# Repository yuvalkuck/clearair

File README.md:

# ClearAir — Intelligent AC Vent Fan Controller

An industrial-grade, real-time environmental control and safety monitoring system running on the **STM32G4** platform. The project is designed to capture ambient air particulates and track highly toxic electrode gases generated during industrial processes (such as welding, EDM, or plasma cutting) to dynamically regulate an AC ventilation fan using a solid-state TRIAC module.

---

## 📑 Table of Contents

- [System Architecture Overview](#-system-architecture-overview)
- [Power & Logic Integration](#-power--logic-integration)
  - [Power Budget (estimate)](#power-budget-estimate)
- [Target Gases & Environmental Indices](#-target-gases--environmental-indices)
  - [Planned Control Indices](#planned-control-indices)
- [Hardware Peripheral Mapping](#️-hardware-peripheral-mapping)
- [Software Architecture](#-software-architecture)
  - [Planned Safety Latch State Machine](#planned-safety-latch-state-machine)
  - [Execution Strategy](#execution-strategy)
  - [Message-queue asynchronous flow](#message-queue-asynchronous-flow)
  - [Sensor-Level Fan Control](#sensor-level-fan-control)
  - [Evacuate alarm](#evacuate-alarm)
- [Compensation & Normalization Models](#-compensation--normalization-models)
- [Safety Core & Fail-Safes](#-safety-core--fail-safes)
- [Roadmap](#️-roadmap)
- [STM32G474CEU6 Pin Plan (WeAct G4 Long)](#-stm32g474ceu6-pin-plan-weact-g4-long)
  - [Service → Pin Assignments](#service--pin-assignments)
  - [Reserved Pins (board / debugger — do not assign)](#reserved-pins-board--debugger--do-not-assign)
  - [Conflict Check](#conflict-check)

---

## 🚀 System Architecture Overview

To protect sensitive metal-oxide gas sensors from destructive metallic dust and electrode debris while keeping ambient tracking responsive, ClearAir uses a **dual-zone sampling topology**:

```mermaid
graph TD
    Ambient[Ambient Air] -->|Direct Ambient Draw| SPS30[Open Air Zone: SPS30 Sensor Element]
    Ambient -->|3-Meter Physical Pipeline| Filter[3M 2091 P100 Particulate Filter]
    Filter -->|Flow Restriction| FanF[Front Fan: 80 mm, 4-pin PWM]
    FanF -->|Pneumatic Delay Delivery| Chamber[Shielded Gas Chamber]
    
    subgraph Isolated Chamber
        Chamber --> MQ131[MQ131 Ozone Sensor]
        Chamber --> MiCS[MiCS-4514 CO / NO2 Sensor]
        Chamber --> BME680[BME680 Environmental Sensor]
    end

    Chamber -->|Exhaust| FanR[Rear Fan: 80 mm, 4-pin PWM, low-rpm standby]

    style Isolated Chamber fill:#f9f9f9,stroke:#333,stroke-width:2px
```

*   **Ambient Air Zone:** The `SPS30` particulate matter sensor rests directly in unshielded ambient air to capture raw particulate mass values before any extraction or filtration happens.
*   **Shielded Gas Chamber:** The `MQ131`, `MiCS-4514`, and `BME680` sensors are isolated inside an analytical testing container. A front fan pulls air through a 3-meter tube and draws it across a **3M 2091 P100 filter**. This removes 99.97% of airborne dust and metallic shards, delivering clean target gases to the metal-oxide sensor elements.
*   **Fans:** Two identical 80 mm (8025), 12 V, 4-pin PWM fans (Cooler Master `FA08025M12LPA` class, about 5800 rpm at full speed, about 0.66 A each). Both run all the time: the front fan sets the sampling flow, at a speed well below its 5800 rpm maximum. The rear fan, at the exhaust end of the chamber, runs at a low speed and keeps the chamber near ambient pressure. If the front fan's tach signal shows a failure, the rear fan speeds up so air still passes through the filter and the sensors are not exposed to unfiltered air. This failover is planned and not implemented in firmware yet. Each fan has its own PWM output and tach input (see the pin plan below).

---

## ⚡ Power & Logic Integration

*   **Mains Split & Supply Rails:** The 220VAC mains feed splits two ways: one branch goes to the RobotDyn TRIAC dimmer (fan phase control), the other to two AC-DC power supply modules, each 2 A and 36.4 x 70 x 23 mm: one outputs **12V** (safety buzzer and both 80 mm fans) and one outputs **5V** (WeAct G474CE Long board via its `P3` 5V pad, plus all sensors, the RobotDyn logic side, and the front-panel WS2812B LEDs). The **3.3V** rail comes from the WeAct board's on-board regulator. Both 80 mm fans run from the 12V rail through the relay `K1` (Panasonic ALDP112, 12 V coil, 1 Form A, 3 A at 30 V DC): the relay contact feeds the fans' 12V pins (`M2` and `M3` pin 2, net `FAN_12V`), so they run whenever the relay is closed. `PB5` (`FILTER_FAN_POWER`) drives `Q6` (2N2222A) through `R41` (1 kΩ); `Q6` switches the coil to GND, `D3` (1N4148) is the flyback diode and `R44` (10 kΩ) keeps the relay open while the pin is not driven, so the fans have no power until the firmware sets `PB5` high. Each fan's PWM and tach wires go to the STM32 (see the pin plan); the fan GND is common with the STM32 GND.
*   **Electrical Noise Isolation:** The internal 5V heating elements of the gas sensors are powered directly from the external 5V supply rail rather than drawing from the MCU. This layout keeps heavy electrical switching current ripples completely away from the sensitive STM32 analog circuitry.
*   **Logic Interfacing:** The `I2C1` bus uses 4.7 kΩ pull-up resistors tied strictly to the STM32's 3.3V rail. The 5V-powered modules (MQ131, MiCS-4514, RobotDyn dimmer) send their outputs (MQ131 `AO`, MiCS-4514 `RED`/`NOX`, RobotDyn `Z-C`) through passive 1.8 kΩ (series) / 3.3 kΩ (to GND) voltage dividers, which drop a 5V signal to ~3.24V, under the 3.3V GPIO/ADC limit.
*   **Front Panel:** The STM32 drives the panel itself; there is no second controller. Six WS2812B RGB LEDs (5 V, one per metric: IAQ, O3, PM2.5, PM10, CO, NO2) form one chain on header `J9` (1 +5V, 2 DIN, 3 GND). Their data comes from `PA6` (`LED_DATA`, `TIM16_CH1` PWM fed by DMA at 800 kHz) through one gate of a 74AHCT125N (`U6`, in a DIP-14 socket, powered from 5 V), because the WS2812B needs at least 0.7 x 5 V = 3.5 V on DIN, more than a 3.3V pin gives. A 330 Ω resistor (`R25`) sits in series with DIN, `C27` (220 µF) buffers the LED supply at `J9`, and `C26` (100 nF) decouples `U6`. The three unused gates have their inputs on GND and `OE` on +5V. Each LED shows its metric's danger level by color and blinks while the buzzer alarm runs; the firmware caps the brightness. An I2C text display connects to header `J10` (1 3V3, 2 GND, 3 SDA, 4 SCL) on `I2C2`, shared with the RTC; the firmware does not use it yet, and once it does, the RTC driver needs a bus lock. Use a 3.3V display (OLED), or remove the 5V pull-ups of an LCD backpack. Four push buttons connect to header `J11` (1-4 `KEY1`-`KEY4`, 5 GND); each button shorts its pin to GND. The resistor ladder is on the board: `R26` (10 kΩ) pulls the `PB11` node (`BUTTONS_ADC`, `ADC2_IN14`) up to 3.3V, and each key pin connects to that node through its own resistor (`R27` 1 kΩ, `R28` 3.3 kΩ, `R29` 6.8 kΩ, `R30` 15 kΩ), so one ADC pin reads all four keys: none 3.30 V, KEY1 0.30 V, KEY2 0.82 V, KEY3 1.34 V, KEY4 1.98 V. `C28` (100 nF) filters the node. With two keys pressed, the lower-numbered key wins. The firmware does not read the keys yet. Four more push buttons, `SW3`-`SW6`, sit on the board as test buttons with a second ladder on `PA4` (`FORCE_STATES_SW`, `ADC2_IN17`): `R31` (10 kΩ) pulls the node up to 3.3V, `R32` 1 kΩ, `R33` 3.3 kΩ, `R34` 6.8 kΩ and `R35` 15 kΩ connect the keys, `C29` (100 nF) filters it, so the levels are the same as above. They test the system: `TEST1` fan off, `TEST2` lower fan speed, `TEST3` higher fan speed, `TEST4` 100% fan plus the buzzer. A standby push button `SW7` (on board) and the 2-pin header `J12` (1 `STANDBY_SW`, 2 GND, for an external switch) are wired in parallel to `PB1` (`STANDBY_SW`); either one pulls the pin to GND, and the MCU pull-up holds it high. Standby is meant to turn off all fans (`PB5` low opens the relay `K1`, and the AC fan stays off) and the buzzer; the firmware does not do this yet. A press only counts when the button is released: the standby event fires on the release, after debounce, and each event toggles standby and the LEDs. Two through-hole status LEDs sit on the board, both on `PB0` (`STANDBY_LED`) with no transistor: the red `D2` goes from the `PB0` node through `R38` (330 Ω) to GND, the green `D1` goes from 3V3 through `R37` (330 Ω) to the `PB0` node, and `R40` (2.2 kΩ) pulls the node up to 3V3. The red LED is therefore on by default, also while the MCU resets and its pin floats; `PB0` high keeps red on and green off, `PB0` low turns red off and lights green. The safety buzzer stays on its own GPIO (see Safety Core & Fail-Safes), so it still sounds if the LEDs or the display fail.
*   **Real-Time Clock (RTC):** A PCF8563 on a HW-689 module (I2C address 0x51, 1.0 to 5.5 V) has its own bus, `I2C2` (`PC4` SCL, `PA8` SDA), with 4.7 kΩ pull-ups to 3.3V; its `COT` and `INT` pins stay unconnected. Only the RTC task uses that bus, so it needs no lock shared with the sensor tasks. The module sits off the perfboard and connects through the 4-pin header `J7` (VCC 3V3, GND, SDA, SCL). A CR1220 cell on the module keeps the clock running during a power loss. Before fitting a non-rechargeable cell, power the module with no cell and check that the cell's + contact reads about 0 V: some RTC modules charge the cell, which would damage a CR1220. The driver is `device/rtc` (`ClockRtc`). Only elapsed time matters, so the clock is never set to the real time: if the `VL` bit says the clock was lost, it restarts at 2000-01-01 00:00. The `rtcTask` writes a "last alive" stamp (minute, hour, day, weekday) once a minute into the four alarm registers, with every alarm-enable bit off so the alarm never fires. At boot, `configure()` compares the clock with the stamp: under 1 hour offline means the 30 minute MQ131 warm-up, and 1 hour or more, a lost clock, an unreadable stamp or an RTC that does not answer means the 48 hour preheat. The stamp has no month, so a gap is only counted when the stamp is from the same day or the day before. The `PB14` button still forces the cold boot. A power cut during the 48 hour preheat followed by a restart under 1 hour later only gets the 30 minute warm-up.
*   **Gas Sensor Heaters:** The MQ131 heater needs a constant 5 V (datasheet: VH 5.0 V ±0.1 V, 34 Ω, up to 900 mW) and over 48 h of preheat after a cold start, so the module VCC and GND are wired straight to the 5 V rail and GND: it is always on and nothing switches it. The MiCS-4514 heaters run on constant power from VCC through the module's own resistors (82 Ω RED, 51 + 82 Ω OX). Its `PRE` pin is tied to GND, so the boost (which shorts the 51 Ω and runs the OX heater near 75 mW, above the 50 mW maximum) is never used. Tie `PRE` to GND only after checking it has the 100 kΩ pull-down to GND (unpowered, `PRE` to GND about 100 kΩ).

### Power Budget (estimate)

Typical datasheet values, not measurements (±20%). STM32 at 170 MHz (`clearair.ioc`).

**5V rail**

| Load | Typical | Peak / max |
| :--- | :--- | :--- |
| WeAct G474CE Long (STM32G474 @ 170 MHz + on-board regulator + user LED; the 3.3V LDO passes the 3V3 load through, so it is counted in the next row) | ~40 mA | 60 mA |
| 3V3 loads via the on-board regulator (BME680 incl. gas-heater pulses, I2C pull-ups, fan tach pull-ups, PCF8563 RTC, two button ladders 0.3 mA max each, green or red status LED about 3-4 mA, `R40` pull-up 1.5 mA while `PB0` is low, `R41` base current 2.6 mA while the fans run) | ~11 mA | 22 mA |
| SPS30 (measuring) | 60 mA | 80 mA |
| MQ131 heater + module (always on, 5 V) | ~170 mA | 185 mA |
| MiCS-4514 (RED + OX heaters + module, `PRE` tied to GND, no boost) | ~60 mA | 65 mA |
| RobotDyn logic side (Z-C opto + PSM) | ~5 mA | 15 mA |
| 1.8k/3.3k dividers (×4) | ~5 mA | 5 mA |
| 74AHCT125N level shifter (`U6`) | <1 mA | 1 mA |
| WS2812B LEDs on `J9` (×6; about 1 mA idle each, one color at reduced brightness typical, all white at full brightness max) | ~70 mA | 360 mA |
| I2C display on `J10` (3.3V OLED, not fitted yet; through the 3.3V regulator) | ~20 mA | 30 mA |
| **Total** | **~440 mA ≈ 2.2 W** | **~830 mA ≈ 4.1 W** |

The 5V total has no fan, because both fans run from the 12V rail. The STLINK-V3MINIE debugger is powered over its own USB and only senses the board's 3.3V on `T_VCC`, so it adds no load to either rail. The G474 board row is an estimate, not a datasheet value: measure the board current on the bench.

**12V rail**

| Load | Typical | Peak / max |
| :--- | :--- | :--- |
| 12V buzzer (active type, only while the alarm sounds) | 30 mA | ~100 mA (loud siren type) |
| Front 80 mm fan (4-pin PWM) | not measured, below the label current at reduced speed | ~660 mA (label) |
| Rear 80 mm fan (4-pin PWM) | not measured, below the label current at low speed | ~660 mA (label) |
| Relay `K1` coil (ALDP112, 720 Ω, while the fans run) | 17 mA | 17 mA |
| **Total** | **not measured** | **~1.44 A ≈ 17 W** |

**PSU sizing:** 5V ≥ 1 A, 12V ≥ 1.5 A. The two 2 A modules cover both rails: the 5V module has about 3 times margin over the 0.61 A peak, and the 12V module has about 30% margin over the 1.44 A peak, so measure the real fan current and the startup surge on the bench. The extra 5V headroom covers cold-heater inrush on the MQ131 and MiCS-4514. The gas-sensor heaters are ~50% of the 5V load (230 of 450 mA typical). The fan rows use the label current quoted in the listing; replace them with measured values.

---

## 📊 Target Gases & Environmental Indices

| Sensor | Target Media | Application / Electrode Coverage |
| :--- | :--- | :--- |
| **SPS30** | PM1.0, PM2.5, PM4.0, PM10 | Monitors metallic fumes, hexavalent chromium particulates, manganese dust, and airborne ash before it reaches the filters. |
| **MQ131** | Ozone ($O_3$) | Tracks $O_3$ gas generated by intense ultraviolet (UV) radiation when open electric arcs ionize ambient oxygen molecules. |
| **MiCS-4514** | Carbon Monoxide ($CO$) & Nitrogen Dioxide ($NO_2$) | Measures toxic shielding gas breakdown products, incomplete combustion ($CO$), and high-temperature thermal fixation byproducts ($NO_2$). |
| **BME680** | VOCs, Sulfur Compounds, $H_2$ Gas | Utilizes the **Bosch BSEC2 library** to track complex vapor emissions coming from cutting fluids, dielectric oils, and insulating resins. |

### Planned Control Indices

Not implemented yet. Fan control today uses per-metric thresholds with no blended index (see [Sensor-Level Fan Control](#sensor-level-fan-control)).

*   **Chamber Air Quality Index (AQI):** A multi-variable matrix blending $CO$, $NO_2$, and BSEC2 $VOC$ data into a single risk metric to determine basic ventilation speeds.
*   **Oxidizing Gas Index (OGI):** A high-priority index tracking the sum of $O_3$ and $NO_2$ gas streams, mirroring extreme electrode ionization states.
*   **Filter Loading Index (FLI):** Calculated from the delta ratio between raw outdoor $SPS30$ values and internal $BME680$ barometric pressure drops, triggering a warning when the physical filter element is clogged.

---

## 🛠️ Hardware Peripheral Mapping

The full wiring schematic is in [`hardware/WeAct-G474CE-Long/clearair.kicad_sch`](hardware/WeAct-G474CE-Long/clearair.kicad_sch) (KiCad 10).

The pin assignments (STM32G474) are in [Service → Pin Assignments](#service--pin-assignments). The old NUCLEO-F446RE board is documented in [`doc/board_stm32f466.md`](doc/board_stm32f466.md).

---

## 🧠 Software Architecture

The software stack runs on top of a priority-preemptive FreeRTOS kernel. It segments slower sensor processing delays from the real-time, time-critical AC phase-angle modulation routines:

```mermaid
graph TD
    %% High-Voltage Side
    subgraph HV [HIGH-VOLTAGE AC SIDE - 50Hz]
        AC_Mains[220V Mains AC]
        AC_Fan[AC FAN MOTOR]
    end

    %% Low-Voltage Side
    subgraph LV [LOW-VOLTAGE CONTROL SIDE - 5V / 3.3V / 12V]
        %% Power Domain
        PSU[AC-DC PSU 12V / 5V]
        Power_5V[5V Power Rail]
        Power_12V[12V Power Rail]
        LDO_33[WeAct On-Board 3.3V Regulator]
        Buzzer_12[12V BUZZER]
        Fan_Front[Front Fan: 80 mm 4-pin PWM]
        Fan_Rear[Rear Fan: 80 mm 4-pin PWM]
        Trans_2N2222[NPN 2N2222A Transistor]
        GND[System GND]
        
        %% Microcontroller Internal Modules
        subgraph STM32 [STM32G4 MCU]
            EXTI[EXTI Line]
            Timer_B[Timer B Phase-Cut]
            PWM_T[TIM1 PWM 25 kHz: CH3 PA10, CH2 PA9]
            Tach_T[TIM2 input capture: CH1 PA5, CH2 PB3]
            subgraph RTOS [FreeRTOS Tasks]
                T1[Task 1: SPS30]
                T2[Task 2: BME680]
                T3[Task 3: MQ131]
                T4[Task 4: MiCS4514]
                T5[Task 5: Central Control]
            end
        end
        
        %% Isolation Barriers
        ZC_Circ[Zero-Crossing Circuit]
        TRIAC_Dim[Isolated TRIAC Dimmer]
    end

    %% Manual Controls
    Reset_Btn[External Reset Button]
    BootSel_Btn[External Boot-Select Button]

    %% Future Visualization Stage
    subgraph VIZ [FRONT PANEL]
        Level_Shift[74AHCT125N 3.3V to 5V buffer]
        LED_Array[6x WS2812B status LEDs]
        Display[I2C display on J10, future]
    end

    %% Power Routing Connections
    AC_Mains -->|Mains Feed| ZC_Circ
    AC_Mains -->|Mains Feed| TRIAC_Dim
    AC_Mains -->|Mains Feed| PSU
    PSU --> Power_5V
    PSU --> Power_12V
    Power_5V -->|P3 5V pad| LDO_33
    LDO_33 -->|3.3V Core VCC| STM32
    Power_12V -->|12V VCC| Buzzer_12
    Power_12V -->|12V + GND| Fan_Front
    Power_12V -->|12V + GND| Fan_Rear

    %% Fan Speed Control and Tach Feedback (firmware not implemented yet)
    PWM_T -->|PWM, PA10| Fan_Front
    PWM_T -->|PWM, PA9| Fan_Rear
    Fan_Front -->|Tach, PA5, 10k pull-up to 3.3V| Tach_T
    Fan_Rear -->|Tach, PB3, 10k pull-up to 3.3V| Tach_T

    %% Signal and Control Connections
    ZC_Circ -->|Opto-Isolated Pulse| EXTI
    EXTI -->|Trigger Reset| Timer_B
    Timer_B -->|Opto-Isolated Gate| TRIAC_Dim
    TRIAC_Dim -->|Phase-Cut Output| AC_Fan
    
    T5 -->|GPIO Output| Trans_2N2222
    Buzzer_12 -->|Low side| Trans_2N2222
    Trans_2N2222 -->|Emitter| GND

    T5 -->|PA6 TIM16 PWM + DMA| Level_Shift
    Level_Shift -->|5V DIN, 330 ohm| LED_Array
    T5 -->|I2C2 PC4/PA8, future| Display

    Reset_Btn -->|NRST| STM32
    BootSel_Btn -->|PB2, read once at boot| STM32
```
### Planned Safety Latch State Machine

This is the intended design, **not what the firmware does today**. The implemented behavior is in [Sensor-Level Fan Control](#sensor-level-fan-control): there is no 30 s countdown, no latch, and the buzzer turns off again when the air improves. The latch and the manual-reset requirement are still to do.

```mermaid
stateDiagram-v2
    [*] --> STATE_NORMAL
    
    state STATE_NORMAL {
        [*] --> WakeUp
        WakeUp --> Receive_Queue : New Reading Posted
        Receive_Queue --> Update_Latest
        Update_Latest --> Calculate_Fan_Curves
        Calculate_Fan_Curves --> Check_Max_Speed : Find Maximum Target Speed (0-100%)
    }
    
    Check_Max_Speed --> STATE_NORMAL : Target Speed < 100%\n[Set FanSpeed = Target Speed, Reset Counter = 30s]
    Check_Max_Speed --> STATE_VENTING_MAX : Target Speed == 100%\n[Set FanSpeed = 100%, Load Counter = 30s]
    
    state STATE_VENTING_MAX {
        [*] --> Evaluate_Trends
        Evaluate_Trends --> Reset_Counter : Metrics improving vs previous second
        Reset_Counter --> Check_Threshold : Values drop below 100%?
        Check_Threshold --> STATE_NORMAL : Yes
        Check_Threshold --> Evaluate_Trends : No
        
        Evaluate_Trends --> Decrement_Counter : Metrics flat or rising
        Decrement_Counter --> Check_Timeout
        Check_Timeout --> Evaluate_Trends : Counter > 0
    }
    
    Check_Timeout --> STATE_EVACUATE_LATCHED : Counter == 0
    
    state STATE_EVACUATE_LATCHED {
        [*] --> Lock_System
        Lock_System --> Force_Buzzer_High : Drive Buzzer GPIO Pin HIGH
        Force_Buzzer_High --> Stay_Locked : Fan locked at 100% / Ignore sensors
        Stay_Locked --> [*] : Requires Manual Hardware Reset
    }

```
### Execution Strategy
*   **Boot Mode Selection:** Before any sensor `configure()` call runs, `appStartDefaultTask` reads the `PB2` boot-select button once and then configures the RTC (`device/rtc`). It's a cold boot when the button is held, or when the RTC shows 1 hour or more offline (or cannot tell, see Real-Time Clock above); otherwise a warm boot. On a warm boot, MQ131 and MiCS-4514 run their normal (short) warm-up before publishing readings; on a cold boot, each runs its own extended warm-up/soak in parallel (see `device/o3sensor` and `device/co1no2`) — none of this is persisted across reboots.
*   **Aggregate Update Cadence:** Individual sensor tasks post to the queue at their own native rate (`SPS30` every 1.0s, `BME680` every 3.0s, `MQ131`/`MiCS-4514` every 20ms), but the system as a whole pushes an updated aggregate `CollectedAirData` snapshot roughly every ~5 seconds for downstream consumers (telemetry, the status LEDs, and the future display).
*   **Low-Overhead Data Capture:** `ADC1` runs continuously in multi-channel Scan Mode handled via DMA. It updates a local 3-element array in RAM with fresh voltages from the `MQ131` and `MiCS-4514` sensors without generating any CPU overhead.
*   **AC Phase Control Loop:** (implemented in `device/fanmotor`, it bypasses the RTOS)
    1. The AC power wave crosses zero volts and the RobotDyn zero-cross output pulls the `ZC_INPUT` pin low.
    2. The falling-edge external interrupt runs `HAL_GPIO_EXTI_Callback`, which calls `onZeroCross()`. If the fan speed is 0 it returns and the gate stays low.
    3. Otherwise it resets the `TIM3` counter, loads the current phase delay into `TIM3->ARR` and starts the `TIM3` update interrupt.
    4. When `TIM3` expires, its interrupt calls `onGateCompareMatch()`, which pulses the TRIAC gate pin (`TRIAC_DIMMER`) high for about 100 µs.
    5. `speedPercent()` (called from the control loop) sets the delay: 50% maps to a long delay (low power) and 100% to a short one, see [Sensor-Level Fan Control](#sensor-level-fan-control).

---

### Message-queue asynchronous flow
```mermaid
graph TD
    %% Asynchronous Inputs
    subgraph Loops [ASYNCHRONOUS INDEPENDENT SENSOR LOOPS]
        T1[Task 1: SPS30 Particulate I2C]
        T2[Task 2: BME680 Gas Plate I2C]
        T3[Task 3: MQ131 Ozone Analog ADC]
        T4[Task 4: MiCS4514 Dual Gas Analog]
    end

    %% Central Message Queue
    subgraph Buffer [FREERTOS MESSAGE QUEUE]
        direction TB
        Queue[[xSensorQueue]]
    end

    %% Sync / Control Layer
    subgraph Decision [PROCESSING & DECISION ENGINE]
        T5[Task 5: Central Controller — evaluates each reading on arrival]
        FanSpeed[Global Fan Speed Variable 0-100%]
        BuzzerPin[GPIO Pin Latch to 2N2222A Base]
        LED_Out[WS2812B status LEDs via TIM16 + DMA]
    end

    %% Hardware Real-Time Layer
    subgraph ISR_Layer [REAL-TIME HARDWARE TIMING LAYER - Bypasses RTOS]
        ZC_Pulse[Zero-Crossing Pulse Input]
        EXTI_ISR[EXTI Hardware Interrupt]
        Timer_ISR[STM32 Timer B Interrupt]
        TRIAC_Gate[Fires Pulse to Isolated TRIAC]
    end

    %% Async Data flow
    T1 -->|Posts reading every 1.0s| Queue
    T2 -->|Posts reading every 3.0s| Queue
    T3 -->|Posts reading every 20ms| Queue
    T4 -->|Posts reading every 20ms| Queue

    %% Central Decision flow
    Queue -->|Receives Each Reading| T5
    T5 -->|Updates| FanSpeed
    T5 -->|Drives HIGH at Evacuate level| BuzzerPin
    T5 -->|Level color per metric| LED_Out

    %% Precise Timing Hardware Loop
    ZC_Pulse --> EXTI_ISR
    EXTI_ISR -->|Resets and Restarts| Timer_ISR
    FanSpeed -.->|Read microsecond duration| Timer_ISR
    Timer_ISR -->|Delays Phase-Cut| TRIAC_Gate
```

### Sensor-Level Fan Control

The control loop (`mainSensorsMsgLoop` in `Core/Src/control_center.cpp`) turns every sensor reading into a danger level and a requested fan speed. The fan follows the worst metric.

**Per metric.** Each metric (BME680 IAQ, MQ131 ozone, SPS30 PM2.5, SPS30 PM10, MiCS-4514 CO, MiCS-4514 NO2) has four thresholds, in the metric's own unit:

| Threshold | Meaning |
| :--- | :--- |
| `fanOff` | A running fan keeps running until the reading drops below this value. It sits slightly below `fanOn`, so the fan does not switch on and off when a reading hovers around the turn-on point. |
| `fanOn` | A stopped fan turns on, at the minimum speed (50%), when the reading reaches this value. |
| `fanMax` | The fan reaches 100% at this value. Between `fanOn` and `fanMax` the speed rises linearly from 50% to 100%. |
| `evacuate` | At or above this value the evacuate alarm starts (see [Evacuate alarm](#evacuate-alarm)). It is at or above `fanMax`, so the fan is already at full speed when the alarm sounds. |

These give each metric one of three danger levels:

| Level | Condition | Fan | Buzzer |
| :--- | :--- | :--- | :--- |
| `Off` | Below `fanOn` (or below `fanOff` if the fan is already running) | Off | Off |
| `Ventilate` | From `fanOn` up to `evacuate` | 50% to 100%, proportional to the reading | Off |
| `Evacuate` | At or above `evacuate` | 100% | Alarm: 60 s on, then 30 s off / 10 s on repeating |

**Across metrics.** Every reading that arrives updates only its own metrics in a shared structure that holds the latest level and requested fan speed of each metric. When the loop finishes handling a message, it evaluates the whole structure: the fan speed is the highest requested by any metric, and the evacuate alarm starts if any metric is at `Evacuate`. The fan and buzzer are only written when the result changes.

**Kick-start.** A stopped motor cannot start at 50% speed. When the fan turns on from off, it first runs at 100% for a fixed spin-up time (`FAN_KICKSTART_MS`), then drops to the requested speed. The fan has no tachometer, so this is a timer, not a measured speed. If the air becomes clean during the spin-up, the fan stops straight away. The loop waits on the queue with a timeout while a spin-up runs, so the fan drops to its target on time even if no sensor message arrives.

**Fan speed to power.** The fan speed percentage maps linearly to the TRIAC firing delay in `device/fanmotor` (50% = `TRIAC_MIN_POWER_DELAY_US`, 100% = `TRIAC_MAX_POWER_DELAY_US`). It is not a power percentage. The 8" fan is an 80 W, 220 V capacitor-run AC motor, which stalls or hums at low voltage, so the minimum delay is set to give roughly 60% of mains RMS voltage at the 50% setting. That value is an estimate from the firing-angle curve and must be confirmed on the bench.

```mermaid
flowchart TD
    Msg[Sensor reading arrives on the queue] --> Update[Update only that sensor's metrics:<br/>level + requested fan %]
    Timeout[Spin-up or alarm timer expires<br/>queue wait timeout] --> Eval
    Update --> Eval[Evaluate all metrics]
    Eval --> Worst[Worst level and highest requested fan %]

    Worst --> Lvl{Worst level}
    Lvl --> Alarm[Evacuate alarm cycle<br/>see Evacuate alarm]

    Worst --> Fan{Requested fan %}
    Fan -->|0 and fan stopped| Stay[Fan stays off]
    Fan -->|0 and fan running| Stop[Stop fan, cancel any spin-up]
    Fan -->|more than 0, fan stopped| Kick[Kick-start: set 100%<br/>for FAN_KICKSTART_MS]
    Fan -->|more than 0, fan running| Set[Set requested speed]
    Kick -->|spin-up done| Set
    Set --> Motor[ControllerFanMotor.speedPercent]
    Kick --> Motor
    Stop --> Motor
```

```mermaid
flowchart LR
    R[Sensor reading] --> A{Reading vs thresholds}
    A -->|below fanOn, fan stopped<br/>or below fanOff, fan running| O[Off: fan 0%]
    A -->|fanOn up to fanMax| V1[Ventilate: fan 50% to 100%, linear]
    A -->|fanMax up to evacuate| V2[Ventilate: fan 100%]
    A -->|evacuate or above| E[Evacuate: fan 100% + alarm]
```

### Evacuate alarm

When the worst level reaches `Evacuate`, the buzzer runs a cycle (`updateAlarm()` in `Core/Src/control_center.cpp`):

1. **First sound:** the buzzer is on for `BUZZER_FIRST_SOUND_MS` (60 s).
2. **Pause:** the buzzer is off for `BUZZER_PAUSE_MS` (30 s).
3. **Buzz:** the buzzer is on for `BUZZER_REPEAT_SOUND_MS` (10 s), then the cycle goes back to the pause. Steps 2 and 3 repeat while the air stays at `Evacuate`.
4. If every metric drops below `evacuate` during a pause, the buzzer gives the safe signal (`BUZZER_SAFE_STEPS_MS`): 1 s of silence, three 2 s beeps with 2 s gaps, a 6 s stop, then three more 2 s beeps with 2 s gaps. The alarm then stops.

The air is only checked during the pause, so a sound or buzz period always runs in full. All the timings, the safe-signal pattern and the pin level that sounds the buzzer (`BUZZER_ON`) are constants at the top of the alarm code, so they are easy to change.

```mermaid
stateDiagram-v2
    [*] --> Idle
    Idle --> AlarmOn : worst level = Evacuate
    AlarmOn --> Pausing : after BUZZER_FIRST_SOUND_MS (60 s)
    Pausing --> SafeBeeps : air below evacuate
    Pausing --> Buzzing : still Evacuate after BUZZER_PAUSE_MS (30 s)
    Buzzing --> Pausing : after BUZZER_REPEAT_SOUND_MS (10 s)
    SafeBeeps --> Idle : 1 s silence, 3 beeps, 6 s stop, 3 beeps
```

**Current limits.** The alarm is not latched: once every metric is below `evacuate` during a pause, it gives the safe signal and stops, unlike the latched `STATE_EVACUATE_LATCHED` in the [planned state machine](#planned-safety-latch-state-machine) above. A metric that has not reported yet counts as `Off`, and there is no stale-data or loss-of-signal handling yet. The MQ131 thresholds are placeholders on raw ADC counts and need calibration, and the other thresholds come from public exposure limits (see the comments next to them in `control_center.cpp`).

## 📉 Compensation & Normalization Models

*   **Pneumatic Lag Tracking:** Air taking a 3-meter path through a dense P100 filter introduces a noticeable physical delay. The control software channels open-air $SPS30$ data packets into an internal software ring buffer. This matches delayed chamber sensor gas metrics with historical particulate conditions.
*   **Environmental Compensation:** Temperature, humidity, and barometric drops alter the baseline resistance ($R_0$) of metal-oxide sensors. ClearAir feeds live ambient calculation layers from the Bosch BSEC2 library into the conversion algorithms to scale raw sensor voltages ($V_{OUT}$ to PPM) relative to the physical conditions inside the chamber.

---

## 🚨 Safety Core & Fail-Safes

**Status:** none of the fail-safes below is implemented yet. The implemented safety behavior is the threshold-based fan ramp and buzzer in [Sensor-Level Fan Control](#sensor-level-fan-control).

*   **Loss of Signal Safeguard:** If the `I2C1` communication lines stall, or if the `ADC1` DMA buffer fails to cycle for 5 consecutive periods, the firmware shifts into an Emergency Override state, locking the TRIAC delay to 0% to force the exhaust fan to run continuously at 100% capacity.
*   **Electrical Fault Monitoring:** If any analog channel detects an out-of-bounds voltage (0V matching a short circuit, or 3.3V matching a ruptured line), the event is reported over telemetry and the ventilation loop steps up to full speed.
*   **Non-Volatile Baseline Recovery:** The system stores the active BSEC2 engine state data matrix to internal flash sectors every hour to prevent calibration degradation during unexpected system power losses.

---

## 🗺️ Roadmap

- [x] 1. **KiCad schematic.** ✅ **Done.** "Create" is a big word here: Claude generated it on request (`hardware/WeAct-G474CE-Long/clearair.kicad_sch`).
- [x] 2. **Move to a WeAct G4 Long** (STM32G474CEU6 Long + STLINK-V3MINIE).
- [x] 3. **Fan and alarm thresholds:** thresholds, fan ramp, kick-start and the evacuation buzzer trigger are implemented (see Sensor-Level Fan Control). Still to do: calibrate the MQ131 thresholds, measure the real minimum fan speed and spin-up time on the bench, latch the alarm, and add stale-data / loss-of-signal handling.
- [ ] 4. **Sensor cylinder:** design and 3D print a cylinder that holds all the sensitive sensors, downstream of a fan with a 3M 2091 particulate filter.
- [ ] 5. **Minimal field test,** with buttons that inject the fan and alarm events.
- [ ] 6. **Power + MCU enclosure:** design and build it (220V AC to 12V and 5V DC).
- [ ] 7. **Full field test** with the welder.

---

## 📌 STM32G474CEU6 Pin Plan (WeAct G4 Long)

Pin map for the **STM32G474CEU6** (UFQFPN48) on the WeAct G4 Long board, debugged with an STLINK-V3MINIE. It is applied in `clear-air.ioc` except for the front and rear fan PWM and tach rows (`TIM1`, `TIM2`), which are still planned. Pin functions come from the CubeMX DB (`STM32G474C(B-C-E)Ux.xml`).

**CubeMX labels used by `device/*`:** `MQ131_ADC`, `MICS_CO1`, `MICS_NO2`, `ZC_INPUT`, `TRIAC_DIMMER`, `BOOT_MODE`, `BUZZER_ON`, `LED_DATA`, `BUTTONS_ADC`, `FORCE_STATES_SW`, `STANDBY_SW`, `STANDBY_LED`, `FILTER_FAN_POWER`, `LED_BOARD`, `I2C_SCL`, `I2C_SDA`, `RTC_SCL`, `RTC_SDA`. The sensor bus handle is `hi2c1` and the RTC bus handle is `hi2c2` (`Core/Src/cpp_main.cpp`).

### Service → Pin Assignments

| Service | Peripheral | G474 Pin (UFQFPN48 pin #) | Notes |
| :--- | :--- | :--- | :--- |
| **SPS30 + BME680** | I2C1 | PA15 SCL (38), PB7 SDA (45) | 4.7 kΩ pull-ups to 3.3V. `PA15` is free because debug uses SWD only (no `JTDI`). |
| **PCF8563 RTC (HW-689)** | I2C2 | PC4 SCL (16), PA8 SDA (30) | Address 0x51, own bus, 4.7 kΩ pull-ups to 3.3V. Standard mode 100 kHz. `COT` and `INT` are not connected. CR1220 backup cell on the module. |
| **MQ-131 Output** | ADC1_IN1 | PA0 (8) | Through the 1.8 kΩ / 3.3 kΩ divider. |
| **MiCS-4514 (CO)** | ADC2_IN2 | PA1 (9) | `PA1` is shared by ADC1/ADC2 IN2. Select ADC2 in CubeMX. |
| **MiCS-4514 ($NO_2$)** | ADC2_IN4 | PA7 (15) | Through the divider. |
| **Buttons (resistor ladder)** | ADC2_IN14 | PB11 (24) | `BUTTONS_ADC`. `R26` 10 kΩ pull-up to 3.3V, keys on `J11` through `R27`-`R30`, `C28` 100 nF to GND. ADC2 regular rank 3, after `MICS_CO1` (rank 1) and `MICS_NO2` (rank 2), 640.5 cycles. |
| **Test buttons (resistor ladder)** | ADC2_IN17 | PA4 (12) | `FORCE_STATES_SW`. `R31` 10 kΩ pull-up to 3.3V, keys `SW3`-`SW6` through `R32`-`R35`, `C29` 100 nF to GND. ADC2 regular rank 4, after `BUTTONS_ADC` (rank 3), 640.5 cycles; `NbrOfConversion` becomes 4. |
| **Standby switch** | GPIO Input | PB1 (18) | `STANDBY_SW`. Pull-up; low = `SW7` or the external switch on `J12` is closed. No EXTI needed (read in a task). |
| **Fan power relay** | GPIO Output | PB5 (43) | `FILTER_FAN_POWER`. Push-pull, initial LOW. HIGH = `Q6` on, relay `K1` closed, both 80 mm fans powered; LOW = fans off. About 17 mA coil current from 12V, 2.6 mA from the pin through `R41`. |
| **Status LED (red / green)** | GPIO Output | PB0 (17) | `STANDBY_LED`. Push-pull, initial HIGH. HIGH or unconfigured = red `D2` on and green `D1` off (`R40` pulls the node up to 3V3); LOW = green on. |
| **RobotDyn ZC Input** | GPIO EXTI12 | PB12 (25) | Falling edge, pull-up, through the divider. Uses the shared `EXTI15_10_IRQn` vector (priority 5); no other EXTI line 10-15 is in use. |
| **RobotDyn Gate Out** | GPIO Output | PB9 (47) | Push-pull, high speed, driven from the `TIM3` ISR. |
| **Cold/Warm Boot Select** | GPIO Input | PB2 (19) | Pull-up, read once at boot. |
| **Safety Buzzer** | GPIO Output | PB10 (22) | Drives the 2N2222A base through R9 (1 kΩ); Q3 switches the 12V buzzer on its low side. HIGH = buzzer on. Initial state LOW. |
| **Front Fan PWM (80 mm)** | TIM1_CH3 | PA10 (32) | 25 kHz PWM to the fan's PWM wire. 1 kΩ in series. Prescaler `0`, period `6799` at 170 MHz. Fan 12V and GND come from the 12V rail, GND common with the STM32. |
| **Rear Fan PWM (80 mm)** | TIM1_CH2 | PA9 (31) | Same timer as the front fan, so the same 25 kHz. 1 kΩ in series. |
| **Front Fan Tach** | TIM2_CH1 | PA5 (13) | Input capture, 10 kΩ pull-up to 3.3V. The tach is an open-collector output; confirm on the bench that the fan does not pull it up to 12V. |
| **Rear Fan Tach** | TIM2_CH2 | PB3 (41) | Input capture, 10 kΩ pull-up to 3.3V. `TIM2` is 32-bit, so a stalled fan does not overflow the period count. |
| **Status Indicator** | GPIO Output | PC6 (29) | On-board WeAct user LED. |
| **Debug & Telemetry** | USART2 | PA2 TX (10), PA3 RX (11) | The board has no on-board ST-LINK, and the 4-pin SWD header has no VCP lines. Wire `PA2`/`PA3` to the STLINK-V3MINIE 14-pin connector (`T_VCP_RX`/`T_VCP_TX`) or to a USB-serial adapter. |
| **Status LEDs (WS2812B chain)** | TIM16_CH1 + DMA | PA6 (14) | PWM at 800 kHz (prescaler `0`, period `211` at 170 MHz), one compare value per bit from DMA. Through `U6` (74AHCT125N at 5 V) and `R25` 330 Ω to `J9` DIN. |
| **Display (future)** | I2C2 (shared with the RTC) | PC4 SCL (16), PA8 SDA (30) | Header `J10`. Not used by the firmware yet. |
| **Phase-Delay Tracking** | TIM3 | Internal | At 170 MHz SYSCLK with APB1 = HCLK, set prescaler `169` for a 1 µs tick. |
| **HAL Timebase** | TIM6 | Internal | `TIM6_DAC_IRQn`. |
| **OS Kernel Clock** | SysTick | Internal | FreeRTOS only. |
| **Manual Reset (external button)** | NRST | PG10-NRST (7) | In parallel with the on-board reset key. |

### Reserved Pins (board / debugger — do not assign)

| Pin | Used by |
| :--- | :--- |
| PA13, PA14 | SWD (`SWDIO`, `SWCLK`). The STLINK-V3MINIE connects to the board's dedicated 4-pin SWD header (3V3, SWDIO, SWCLK, GND) next to the two keys. That header has no `SWO` or `JTDI`, so `PB3` and `PA15` are free. |
| PA11, PA12 | On-board USB-C (`USB_DM`, `USB_DP`) |
| PB8-BOOT0 | BOOT0, wired to the on-board BOOT key |
| PG10-NRST | NRST, wired to the on-board reset key and the external reset button |
| PF0, PF1 | 8 MHz HSE crystal |
| PC14, PC15 | 32.768 kHz LSE crystal |
| PC6 | On-board user LED (used as the status indicator above) |
| PC13 | On-board user key |
| PB4, PB6 | UCPD1 dead-battery pull-downs (`CC2`/`CC1`). Avoided, so they stay free of side effects. |

### Conflict Check

*   Each pin above has one function.
*   The only EXTI line in use is EXTI12 (`PB12`).
*   No alternate function overlaps another selected peripheral. The other I2C1 pin options are not used: `PA13`/`PA14` are SWD and `PB8` is BOOT0. The I2C1 SDA alternate `PB9` is the TRIAC gate GPIO. The I2C1 SMBA pin (`PB5`) stays unused.
*   On the UFQFPN48, `I2C2` is the only second I2C bus that fits: its SDA is on `PA8` or `PF0` (HSE), `I2C3` SCL is only on `PA8`, and `I2C4` needs `PA13`/`PC6`/`PB7`, which are all taken. So the front fan PWM moved from `TIM1_CH1` (`PA8`) to `TIM1_CH3` (`PA10`), and `I2C2` uses `PC4`/`PA8`.
*   `PA9`/`PA10` (`TIM1_CH2`/`TIM1_CH3`) and `PA5`/`PB3` (`TIM2_CH1`/`TIM2_CH2`) were spare. `TIM1` and `TIM2` are not used by anything else in this plan. The CubeMX DB lists these functions for the G474 UFQFPN48.
*   `VREF+` (pin 20) must connect to `VDDA` on the board for the ADCs to read against 3.3V.

*   The ZC input, TRIAC gate, boot button, buzzer and LED data sit on `PB12`, `PB9`, `PB2`, `PB10` and `PA6` (`TIM16_CH1`, a timer nothing else uses) so that SPI2 stays free (SPI3 lost its MOSI pin `PB5` to `FILTER_FAN_POWER`; COMP1, COMP4 and DAC1_OUT1 are taken by `PB1`, `PB0` and `PA4`; COMP2 stays on `PA7`) for later use. SPI1, I2C3, I2C4, COMP3, USART1 and LPUART1 cannot be freed on this package without moving an ADC, fan or I2C pin; UART4 shares `PC10`/`PC11` with SPI3.

**Spare pins after this plan:** PB13, PB14, PB15, PC10, PC11.

| Free service | Pins |
| :--- | :--- |
| SPI2 | `PB13` SCK, `PB14` MISO, `PB15` MOSI (software NSS) |
| COMP2 | INP `PA7` (shared with `MICS_NO2`) |

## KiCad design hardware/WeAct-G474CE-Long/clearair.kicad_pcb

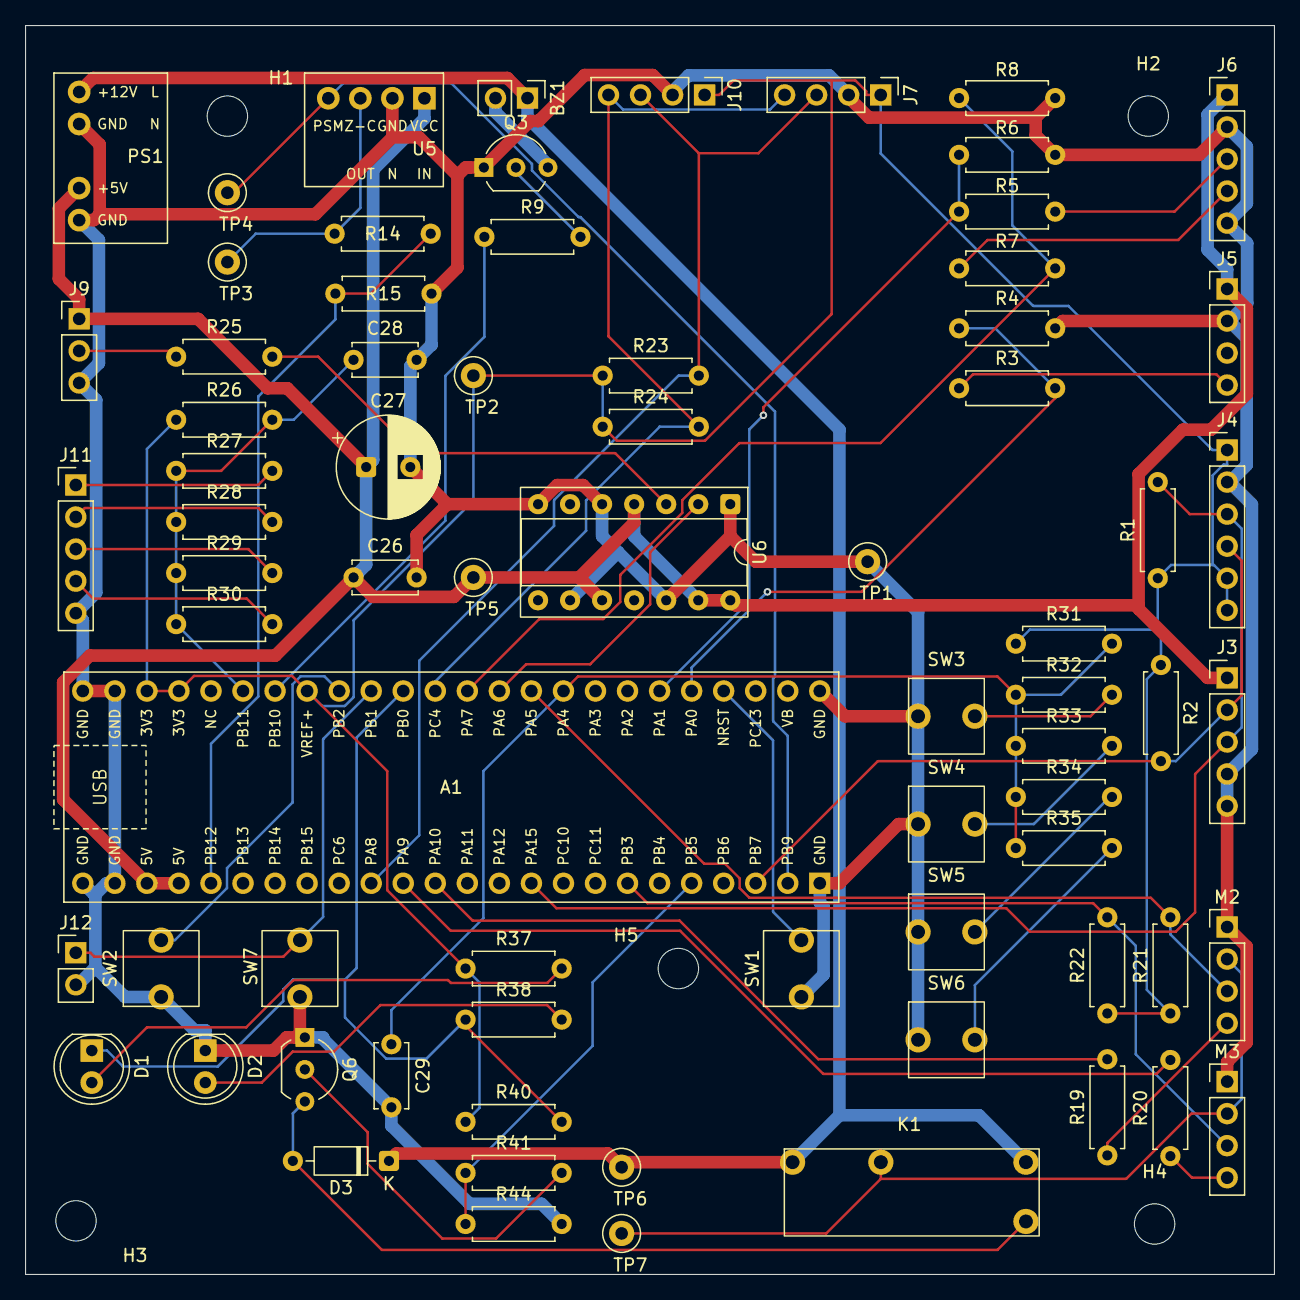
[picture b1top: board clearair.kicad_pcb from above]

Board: 2 copper layers, 99.0 x 99.0 mm, 78 parts (0 on the bottom side), 49 nets.

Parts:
A1: WeAct STM32G474CEU6 Core Board (Long); WeAct_STM32G474CoreBoard_Long
BZ1: 12V buzzer; PinHeader_1x02_P2.54mm_Vertical
C26, C28, C29: 100nF; C_Disc_D5.0mm_W2.5mm_P5.00mm
C27: 220uF; CP_Radial_D8.0mm_P3.50mm
D1: GREEN; LED_D5.0mm
D2: RED; LED_D5.0mm
D3: 1N4148; D_DO-35_SOD27_P7.62mm_Horizontal
H1, H2, H3, H4, H5: M3; MountingHole_3.2mm_M3
J3: SPS30; PinHeader_1x05_P2.54mm_Vertical
J4: BME680; PinHeader_1x06_P2.54mm_Vertical
J5: MQ131; PinHeader_1x04_P2.54mm_Vertical
J6: MiCS-4514; PinHeader_1x05_P2.54mm_Vertical
J7: RTC PCF8563; PinHeader_1x04_P2.54mm_Vertical
J9: WS2812B LEDs; PinHeader_1x03_P2.54mm_Vertical
J10: Display I2C2; PinHeader_1x04_P2.54mm_Vertical
J11: Buttons (1-4 KEY1-4, 5 GND); PinHeader_1x05_P2.54mm_Vertical
J12: Standby ext; PinHeader_1x02_P2.54mm_Vertical
K1: ALDP112; Relay_Panasonic_ALDP112
M2: 80mm fan front; PinHeader_1x04_P2.54mm_Vertical
M3: 80mm fan rear; PinHeader_1x04_P2.54mm_Vertical
PS1: AC-DC PSUs 12V 2A + 5V 2A (DC out); PSU_DC_12V_5V_Inputs
Q3, Q6: 2N2222A; TO-92_Inline_Wide
R1, R2, R23, R24: 4k7; R_Axial_DIN0207_L6.3mm_D2.5mm_P7.62mm_Horizontal
R3, R5, R7, R14: 1k8; R_Axial_DIN0207_L6.3mm_D2.5mm_P7.62mm_Horizontal
R4, R6, R8, R15, R28, R33: 3k3; R_Axial_DIN0207_L6.3mm_D2.5mm_P7.62mm_Horizontal
R9, R19, R20, R27, R32, R41: 1k; R_Axial_DIN0207_L6.3mm_D2.5mm_P7.62mm_Horizontal
R21, R22, R26, R31, R44: 10k; R_Axial_DIN0207_L6.3mm_D2.5mm_P7.62mm_Horizontal
R25, R37, R38: 330; R_Axial_DIN0207_L6.3mm_D2.5mm_P7.62mm_Horizontal
R29, R34: 6k8; R_Axial_DIN0207_L6.3mm_D2.5mm_P7.62mm_Horizontal
R30, R35: 15k; R_Axial_DIN0207_L6.3mm_D2.5mm_P7.62mm_Horizontal
R40: 2k2; R_Axial_DIN0207_L6.3mm_D2.5mm_P7.62mm_Horizontal
SW1: RESET red; SW_Tactile_6x6x5_2pin
SW2: COLD_BOOT white; SW_Tactile_6x6x5_2pin
SW3: TEST1; SW_Tactile_6x6x5_2pin
SW4: TEST2; SW_Tactile_6x6x5_2pin
SW5: TEST3; SW_Tactile_6x6x5_2pin
SW6: TEST4; SW_Tactile_6x6x5_2pin
SW7: STANDBY; SW_Tactile_6x6x5_2pin
TP1: GND; TestPoint_Loop_D2.50mm_Drill1.0mm
TP2: +3V3; TestPoint_Loop_D2.50mm_Drill1.0mm
TP3: ZC_OUT; TestPoint_Loop_D2.50mm_Drill1.0mm
TP4: TRIAC_DIMMER; TestPoint_Loop_D2.50mm_Drill1.0mm
TP5: +5V; TestPoint_Loop_D2.50mm_Drill1.0mm
TP6: +12V; TestPoint_Loop_D2.50mm_Drill1.0mm
TP7: FAN_12V; TestPoint_Loop_D2.50mm_Drill1.0mm
U5: RobotDyn AC dimmer; RobotDyn_Dimmer_Logic
U6: 74AHCT125N; DIP-14_W7.62mm_Socket

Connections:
+3V3: A1.37 (VREF+), A1.47 (3V3), A1.48 (3V3), J4.1 (VCC), J4.5 (SDO), J4.6 (CS), J7.1, J10.1, R1.1, R2.1, R21.1, R22.1, R23.1, R24.1, R26.1, R31.1, R37.1, R40.1, TP2.1 (1_1)
+5V: A1.43 (VDD5V), A1.44 (VDD5V), C26.1, C27.1, J3.1, J5.1, J6.1, J9.1, PS1.4, TP5.1 (1_1), U5.1 (VCC), U6.4, U6.10, U6.13, U6.14 (VCC)
+12V: BZ1.1 (+), D3.1 (K), K1.14, K1.A1, PS1.3, TP6.1 (1_1)
/BOOT_MODE: A1.36 (PB2), SW2.2
/BUTTONS_ADC: A1.39 (PB11), C28.1, R26.2, R27.1, R28.1, R29.1, R30.1
/BUZZER_BASE: Q3.2 (B), R9.2
/BUZZER_NEG: BZ1.2 (-), Q3.3 (C)
/BUZZER_ON: A1.38 (PB10), R9.1
/FAN_12V: K1.13, M2.2, M3.2, TP7.1 (1_1)
/FAN_FRONT_PWM: A1.13 (PA10), R19.2
/FAN_FRONT_PWM_IN: M2.4, R19.1
/FAN_FRONT_TACH: A1.30 (PA5), M2.3, R21.2
/FAN_REAR_PWM: A1.14 (PA9), R20.2
/FAN_REAR_PWM_IN: M3.4, R20.1
/FAN_REAR_TACH: A1.7 (PB3), M3.3, R22.2
/FILTER_FAN_POWER: A1.5 (PB5), R41.1, R44.1
/FORCE_STATES_SW: A1.29 (PA4), C29.1, R31.2, R32.1, R33.1, R34.1, R35.1
/I2C_SCL: A1.10 (PA15), J3.3, J4.3 (SCL), R1.2
/I2C_SDA: A1.3 (PB7), J3.2, J4.4 (SDA), R2.2
/LED_DATA: A1.31 (PA6), U6.2
/MICS_CO1: A1.26 (PA1), R5.1, R6.1
/MICS_CO_OUT: J6.3, R5.2
/MICS_NO2: A1.32 (PA7), R7.2, R8.1
/MICS_NO2_OUT: J6.4, R7.1
/MQ131_ADC: A1.25 (PA0), R3.2, R4.1
/MQ131_OUT: J5.4, R3.1
/NRST: A1.24 (NRST), SW1.2
/RTC_SCL: A1.33 (PC4), J7.4, J10.4, R24.2
/RTC_SDA: A1.15 (PA8), J7.3, J10.3, R23.2
/STANDBY_LED: A1.34 (PB0), D1.1 (K), R38.1, R40.2
/STANDBY_SW: A1.35 (PB1), J12.1, SW7.2
/TRIAC_DIMMER: A1.2 (PB9), TP4.1 (1_1), U5.4 (PSM)
/ZC_INPUT: A1.20 (PB12), R14.1, R15.1
/ZC_OUT: R14.2, TP3.1 (1_1), U5.3 (Z-C)
GND: A1.1 (GND), A1.21 (GND), A1.41 (GND), A1.42 (GND), A1.45 (GND), A1.46 (GND), C26.2, C27.2, C28.2, C29.2, D2.1 (K), J3.4, J3.5, J4.2 (GND), J5.2, J6.2, J6.5, J7.2, J9.3, J10.2, J11.5, J12.2, M2.1, M3.1, PS1.5, Q3.1 (E), Q6.1 (E), R4.2, R6.2, R8.2, R15.2, R44.2, SW1.1, SW2.1, SW3.1, SW4.1, SW5.1, SW6.1, SW7.1, TP1.1 (1_1), U5.2 (GND), U6.1, U6.5, U6.7 (GND), U6.9, U6.12
unnamed: D1.2 (A), R37.2
unnamed: D2.2 (A), R38.2
unnamed: D3.2 (A), K1.A2, Q6.3 (C)
unnamed: J9.2, R25.1
unnamed: J11.1, R27.2
unnamed: J11.2, R28.2
unnamed: J11.3, R29.2
unnamed: J11.4, R30.2
unnamed: Q6.2 (B), R41.2
unnamed: R25.2, U6.3
unnamed: R32.2, SW3.2
unnamed: R33.2, SW4.2
unnamed: R34.2, SW5.2
unnamed: R35.2, SW6.2

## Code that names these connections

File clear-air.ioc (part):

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Mcu.Name=STM32G474C(B-C-E)Ux
Mcu.Package=UFQFPN48
Mcu.UserName=STM32G474CEUx
PA0.GPIOParameters=GPIO_Label
PA0.GPIO_Label=MQ131_ADC
PA0.Mode=IN1-Single-Ended
PA0.Signal=ADC1_IN1
PA1.GPIOParameters=GPIO_Label
PA1.GPIO_Label=MICS_CO1
PA1.Mode=IN2-Single-Ended
PA1.Signal=ADC2_IN2
PA10.GPIOParameters=GPIO_Label
PA10.GPIO_Label=FAN_FRONT_PWM
PA10.Signal=S_TIM1_CH3
PA13.Mode=Serial_Wire
PA13.Signal=SYS_JTMS-SWDIO
PA14.Mode=Serial_Wire
PA14.Signal=SYS_JTCK-SWCLK
PA15.GPIOParameters=GPIO_Label
PA15.GPIO_Label=I2C_SCL
PA15.Mode=I2C
PA15.Signal=I2C1_SCL
PA2.Mode=Asynchronous
PA2.Signal=USART2_TX
PA3.Mode=Asynchronous
PA3.Signal=USART2_RX
PA4.GPIOParameters=GPIO_Label
PA4.GPIO_Label=FORCE_STATES_SW
PA4.Mode=IN17-Single-Ended
PA4.Signal=ADC2_IN17
PA5.GPIOParameters=GPIO_Label
PA5.GPIO_Label=FAN_FRONT_TACH
PA5.Signal=S_TIM2_CH1
PA6.GPIOParameters=GPIO_Label
PA6.GPIO_Label=LED_DATA
PA6.Signal=S_TIM16_CH1
PA7.GPIOParameters=GPIO_Label
PA7.GPIO_Label=MICS_NO2
PA7.Mode=IN4-Single-Ended
PA7.Signal=ADC2_IN4
PA8.GPIOParameters=GPIO_Label
PA8.GPIO_Label=RTC_SDA
PA8.Mode=I2C
PA8.Signal=I2C2_SDA
PA9.GPIOParameters=GPIO_Label
PA9.GPIO_Label=FAN_REAR_PWM
PA9.Signal=S_TIM1_CH2
PB0.GPIOParameters=PinState,GPIO_Label
PB0.GPIO_Label=STANDBY_LED
PB0.PinState=GPIO_PIN_SET
PB0.Signal=GPIO_Output
PB1.GPIOParameters=GPIO_PuPd,GPIO_Label
PB1.GPIO_Label=STANDBY_SW
PB1.GPIO_PuPd=GPIO_PULLUP
PB1.Signal=GPIO_Input
PB10.GPIOParameters=GPIO_PuPd,GPIO_Label
PB10.GPIO_Label=BUZZER_ON
PB10.GPIO_PuPd=GPIO_NOPULL
PB10.Signal=GPIO_Output
PB11.GPIOParameters=GPIO_Label
PB11.GPIO_Label=BUTTONS_ADC
PB11.Mode=IN14-Single-Ended
PB11.Signal=ADC2_IN14
PB12.GPIOParameters=GPIO_PuPd,GPIO_Label,GPIO_ModeDefaultEXTI
PB12.GPIO_Label=ZC_INPUT
PB12.GPIO_ModeDefaultEXTI=GPIO_MODE_IT_FALLING
PB12.GPIO_PuPd=GPIO_PULLUP
PB12.Signal=GPXTI12
PB2.GPIOParameters=GPIO_PuPd,GPIO_Label
PB2.GPIO_Label=BOOT_MODE
PB2.GPIO_PuPd=GPIO_PULLUP
PB2.Signal=GPIO_Input
PB3.GPIOParameters=GPIO_Label
PB3.GPIO_Label=FAN_REAR_TACH
PB3.Signal=S_TIM2_CH2
PB5.GPIOParameters=GPIO_Label
PB5.GPIO_Label=FILTER_FAN_POWER
PB5.Signal=GPIO_Output
PB7.GPIOParameters=GPIO_Label
PB7.GPIO_Label=I2C_SDA
PB7.Mode=I2C
PB7.Signal=I2C1_SDA
PB9.GPIOParameters=GPIO_Speed,GPIO_Label
PB9.GPIO_Label=TRIAC_DIMMER
PB9.GPIO_Speed=GPIO_SPEED_FREQ_HIGH
PB9.Signal=GPIO_Output
PC4.GPIOParameters=GPIO_Label
PC4.GPIO_Label=RTC_SCL
PC4.Mode=I2C
PC4.Signal=I2C2_SCL
PC6.GPIOParameters=GPIO_Label
PC6.GPIO_Label=LED_BOARD
PC6.Signal=GPIO_Output
PF0-OSC_IN.Mode=HSE-External-Oscillator
PF0-OSC_IN.Signal=RCC_OSC_IN
PF1-OSC_OUT.Mode=HSE-External-Oscillator
PF1-OSC_OUT.Signal=RCC_OSC_OUT
RCC.HSE_VALUE=8000000
RCC.SYSCLKFreq_VALUE=170000000
RCC.SYSCLKSource=RCC_SYSCLKSOURCE_PLLCLK
board=custom

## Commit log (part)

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2026-06-21 Initial STM32 project commit
2026-06-21 init
2026-06-22 success blinking
2026-06-22 add readme
